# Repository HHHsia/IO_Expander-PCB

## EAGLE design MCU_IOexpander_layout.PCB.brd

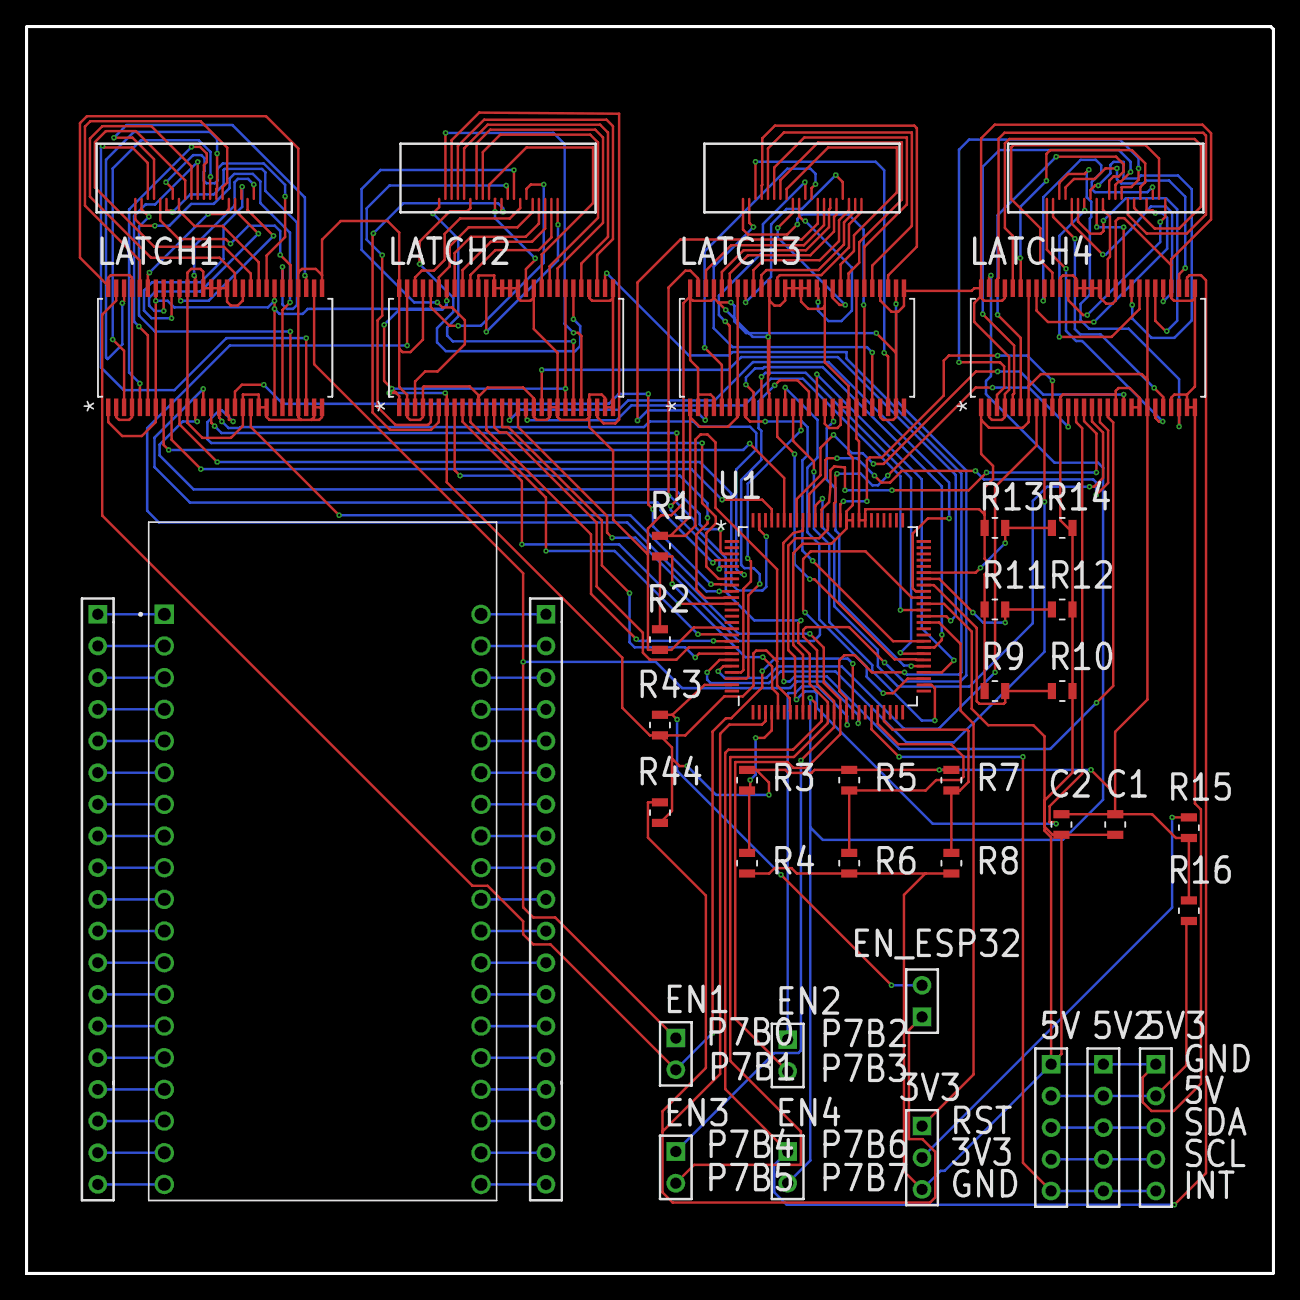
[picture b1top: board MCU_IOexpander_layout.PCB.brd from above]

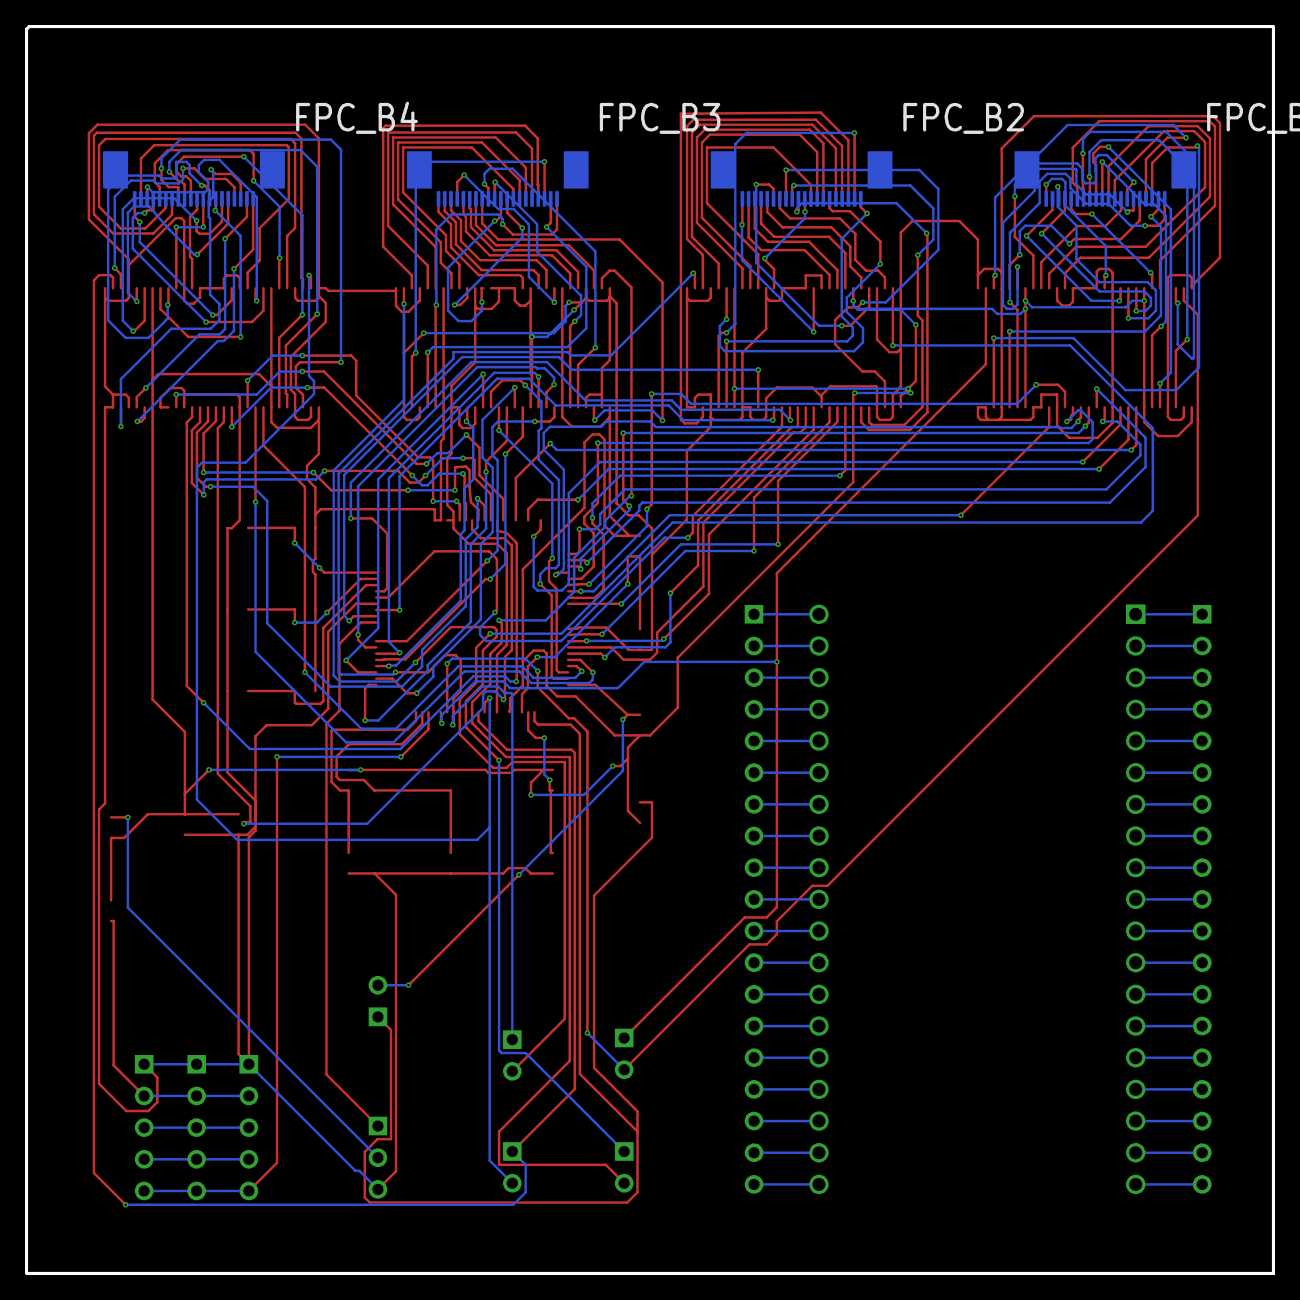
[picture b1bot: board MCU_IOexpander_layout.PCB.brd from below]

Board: 2 copper layers, 100.0 x 100.0 mm, 41 parts (4 on the bottom side), 183 nets.

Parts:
3V3: Header_3; HDR1X3_1PRIMARY
5V, 5V2: Header_5; HDR1X5_1PRIMARY
5V3: Header_5; HDR1X5_2PRIMARY
C1, C2: C0805; RES_RC0805_YAG-L_1PRIMARY
EN1: Header_2; HDR1X2_5PRIMARY
EN2: Header_2; HDR1X2_4PRIMARY
EN3: Header_2; HDR1X2_3PRIMARY
EN4: Header_2; HDR1X2_2PRIMARY
EN_ESP32: Header_2; HDR1X2_1PRIMARY
EN_ESP?, EN_ESP?2: Header_19; HDR1X19_1PRIMARY
FPC_B1: FPC__20PIN_; FPC_20PIN__B_4PRIMARY
FPC_B2: *; FPC_20PIN__B_3PRIMARY
FPC_B3: *; FPC_20PIN__B_2PRIMARY
FPC_B4: *; FPC_20PIN__B_1PRIMARY
LATCH1: SN74ALVCH162260DLR; DL56-L_4PRIMARY
LATCH2: SN74ALVCH162260DLR; DL56-L_3PRIMARY
LATCH3: SN74ALVCH162260DLR; DL56-L_2PRIMARY
LATCH4: SN74ALVCH162260DLR; DL56-L_1PRIMARY
R1, R2, R3, R4, R5, R6, R7, R8, R15, R16, R43: RC0805FR-1310KL; RES_RC0805_YAG-L_2PRIMARY
R9, R10, R11, R12, R13, R14: RC0805FR-1310KL; RES_RC0805_YAG-L_3PRIMARY
R44: RC0805FR-1310KL; RES_RC0805_YAG-L_1PRIMARY
U1: CY8C9560A-24AXI; TQFP-100-L_1PRIMARY
U?: ESP32-DEVKITC-32D; MODULE_ESP32-DEVKITC-32D_1PRIMARY

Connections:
3V3: 3V3.2, R15.2
5V: 5V.2, 5V2.2, 5V3.2, R16.1
A0: R1.1, R2.2, U1.30
FPC_1: FPC_B1.3, LATCH1.23
FPC_2: FPC_B1.4, LATCH1.24
FPC_3: FPC_B1.5, LATCH1.26
FPC_4: FPC_B1.6, LATCH1.31
FPC_5: FPC_B1.7, LATCH1.33
FPC_6: FPC_B1.8, LATCH1.34
FPC_7: FPC_B1.9, LATCH1.36
FPC_8: FPC_B1.10, LATCH1.37
FPC_9: FPC_B1.11, LATCH1.38
FPC_10: FPC_B1.12, LATCH1.40
FPC_11: FPC_B1.13, LATCH1.6
FPC_12: FPC_B1.14, LATCH1.5
FPC_13: FPC_B1.15, LATCH1.3
FPC_14: FPC_B1.16, LATCH1.54
FPC_15: FPC_B1.17, LATCH1.52
FPC_16: FPC_B1.18, LATCH1.51
FPC_17: FPC_B1.19, LATCH1.49
FPC_18: FPC_B1.20, LATCH1.48
FPC_19: FPC_B1.21, LATCH1.47
FPC_20: FPC_B1.22, LATCH1.45
FPC_21: FPC_B2.3, LATCH2.23
FPC_22: FPC_B2.4, LATCH2.24
FPC_23: FPC_B2.5, LATCH2.26
FPC_24: FPC_B2.6, LATCH2.31
FPC_25: FPC_B2.7, LATCH2.33
FPC_26: FPC_B2.8, LATCH2.34
FPC_27: FPC_B2.9, LATCH2.36
FPC_28: FPC_B2.10, LATCH2.37
FPC_29: FPC_B2.11, LATCH2.38
FPC_30: FPC_B2.12, LATCH2.40
FPC_31: FPC_B2.13, LATCH2.6
FPC_32: FPC_B2.14, LATCH2.5
FPC_33: FPC_B2.15, LATCH2.3
FPC_34: FPC_B2.16, LATCH2.54
FPC_35: FPC_B2.17, LATCH2.52
FPC_36: FPC_B2.18, LATCH2.51
FPC_37: FPC_B2.19, LATCH2.49
FPC_38: FPC_B2.20, LATCH2.48
FPC_39: FPC_B2.21, LATCH2.47
FPC_40: FPC_B2.22, LATCH2.45
FPC_41: FPC_B3.3, LATCH3.23
FPC_42: FPC_B3.4, LATCH3.24
FPC_43: FPC_B3.5, LATCH3.26
FPC_44: FPC_B3.6, LATCH3.31
FPC_45: FPC_B3.7, LATCH3.33
FPC_46: FPC_B3.8, LATCH3.34
FPC_47: FPC_B3.9, LATCH3.36
FPC_48: FPC_B3.10, LATCH3.37
FPC_49: FPC_B3.11, LATCH3.38
FPC_50: FPC_B3.12, LATCH3.40
FPC_51: FPC_B3.13, LATCH3.6
FPC_52: FPC_B3.14, LATCH3.5
FPC_53: FPC_B3.15, LATCH3.3
FPC_54: FPC_B3.16, LATCH3.54
FPC_55: FPC_B3.17, LATCH3.52
FPC_56: FPC_B3.18, LATCH3.51
FPC_57: FPC_B3.19, LATCH3.49
FPC_58: FPC_B3.20, LATCH3.48
FPC_59: FPC_B3.21, LATCH3.47
FPC_60: FPC_B3.22, LATCH3.45
FPC_61: FPC_B4.3, LATCH4.23
FPC_62: FPC_B4.4, LATCH4.24
FPC_63: FPC_B4.5, LATCH4.26
FPC_64: FPC_B4.6, LATCH4.31
FPC_65: FPC_B4.7, LATCH4.33
FPC_66: FPC_B4.8, LATCH4.34
FPC_67: FPC_B4.9, LATCH4.36
FPC_68: FPC_B4.10, LATCH4.37
FPC_69: FPC_B4.11, LATCH4.38
FPC_70: FPC_B4.12, LATCH4.40
FPC_71: FPC_B4.13, LATCH4.6
FPC_72: FPC_B4.14, LATCH4.5
FPC_73: FPC_B4.15, LATCH4.3
FPC_74: FPC_B4.16, LATCH4.54
FPC_75: FPC_B4.17, LATCH4.52
FPC_76: FPC_B4.18, LATCH4.51
FPC_77: FPC_B4.19, LATCH4.49
FPC_78: FPC_B4.20, LATCH4.48
FPC_79: FPC_B4.21, LATCH4.47
FPC_80: FPC_B4.22, LATCH4.45
GND: 3V3.3, 5V.1, 5V2.1, 5V3.1, C1.1, C2.1, LATCH1.2, LATCH1.4, LATCH1.11, LATCH1.18, LATCH1.20, LATCH1.21, LATCH1.25, LATCH1.27, LATCH1.28, LATCH1.29, LATCH1.32, LATCH1.39, LATCH1.41, LATCH1.42, LATCH1.43, LATCH1.44, LATCH1.46, LATCH1.53, LATCH1.56, LATCH2.2, LATCH2.4, LATCH2.11, LATCH2.18, LATCH2.20, LATCH2.21, LATCH2.25, LATCH2.27, LATCH2.28, LATCH2.29, LATCH2.32, LATCH2.39, LATCH2.41, LATCH2.42, LATCH2.43, LATCH2.44, LATCH2.46, LATCH2.53, LATCH2.56, LATCH3.2, LATCH3.4, LATCH3.11, LATCH3.18, LATCH3.20, LATCH3.21, LATCH3.25, LATCH3.27, LATCH3.29, LATCH3.32, LATCH3.39, LATCH3.41, LATCH3.42, LATCH3.43, LATCH3.44, LATCH3.46, LATCH3.53, LATCH3.56, LATCH4.2, LATCH4.4, LATCH4.11, LATCH4.18, LATCH4.20, LATCH4.21, LATCH4.25, LATCH4.27, LATCH4.28, LATCH4.29, LATCH4.32, LATCH4.39, LATCH4.41, LATCH4.42, LATCH4.43, LATCH4.44, LATCH4.46, LATCH4.53, LATCH4.56, R2.1, R4.1, R6.1, R8.1, R10.1, R12.1, R14.1, U1.15, U1.34, U1.65, U1.84, U1.85
INT: 5V.5, 5V2.5, 5V3.5, U1.45
J2-1: EN_ESP?2.1, U?.1
J2-2: EN_ESP?2.2, U?.2
J2-3: EN_ESP?2.3, U?.3
J2-4: EN_ESP?2.4, U?.4
J2-5: EN_ESP?2.5, U?.5
J2-6: EN_ESP?2.6, U?.6
J2-7: EN_ESP?2.7, U?.7
J2-8: EN_ESP?2.8, U?.8
J2-9: EN_ESP?2.9, U?.9
J2-10: EN_ESP?2.10, U?.10
J2-11: EN_ESP?2.11, U?.11
J2-12: EN_ESP?2.12, U?.12
J2-13: EN_ESP?2.13, U?.13
J2-14: EN_ESP?2.14, U?.14
J2-15: EN_ESP?2.15, U?.15
J2-16: EN_ESP?2.16, U?.16
J2-17: EN_ESP?2.17, U?.17
J2-18: EN_ESP?2.18, U?.18
J2-19: EN_ESP?2.19, U?.19
J3-1: EN_ESP?.1, U?.20
J3-2: EN_ESP?.2, U?.21
J3-3: EN_ESP?.3, U?.22
J3-4: EN_ESP?.4, U?.23
J3-5: EN_ESP?.5, U?.24
J3-6: EN_ESP?.6, U?.25
J3-7: EN_ESP?.7, U?.26
J3-8: EN_ESP?.8, U?.27
J3-9: EN_ESP?.9, U?.28
J3-10: EN_ESP?.10, U?.29
J3-11: EN_ESP?.11, U?.30
J3-12: EN_ESP?.12, U?.31
J3-13: EN_ESP?.13, U?.32
J3-14: EN_ESP?.14, U?.33
J3-15: EN_ESP?.15, U?.34
J3-16: EN_ESP?.16, U?.35
J3-17: EN_ESP?.17, U?.36
J3-18: EN_ESP?.18, U?.37
J3-19: EN_ESP?.19, U?.38
NETEN_ESP32_1: EN_ESP32.1, R44.2, U1.28
NETEN_ESP32_2: EN_ESP32.2, R43.2, U1.24
P0B0: LATCH1.8, U1.95
P0B1: LATCH1.9, U1.97
P0B2: LATCH1.10, U1.99
P0B3: LATCH1.12, U1.3
P0B4: LATCH1.13, U1.4
P0B5: LATCH1.14, U1.5
P0B6: LATCH1.15, U1.6
P0B7: LATCH1.16, U1.7
P1B5: R13.1, R14.2, U1.70
P1B6: R11.1, R12.2, U1.69
P1B7: R9.1, R10.2, U1.68
P2B0: R7.1, R8.2, U1.47
P2B1: R5.1, R6.2, U1.46
P2B3: R3.1, R4.2, U1.29
P3B0: LATCH1.17, U1.8
P3B1: LATCH1.19, U1.9
P3B2: LATCH2.8, U1.10
P3B3: LATCH2.9, U1.11
P3B4: LATCH2.10, U1.16
P3B5: LATCH2.12, U1.17
P3B6: LATCH2.13, U1.18
P3B7: LATCH2.14, U1.19
P4B0: LATCH2.15, U1.67
P4B1: LATCH2.16, U1.66
P4B2: LATCH2.17, U1.64
P4B3: LATCH2.19, U1.63
P4B4: LATCH3.8, U1.59
P4B5: LATCH3.9, U1.58
P4B6: LATCH3.10, U1.57
P4B7: LATCH3.12, U1.56
P5B0: LATCH3.13, U1.53
P5B1: LATCH3.14, U1.52
P5B2: LATCH3.15, U1.22
P5B3: LATCH3.16, U1.23
P5B4: LATCH3.17, U1.54
P5B5: LATCH3.19, U1.55
P5B6: LATCH4.8, U1.21
P5B7: LATCH4.9, U1.20
P6B0: LATCH4.10, U1.86
P6B1: LATCH4.12, U1.87
P6B2: LATCH4.13, U1.88
P6B3: LATCH4.14, U1.89
P6B4: LATCH4.15, U1.90
P6B5: LATCH4.16, U1.91
P6B6: LATCH4.17, U1.92
P6B7: LATCH4.19, U1.93
P7B0: EN1.1, LATCH1.30, U1.43
P7B1: EN1.2, LATCH1.55, U1.42
P7B2: EN2.1, LATCH2.30, U1.41
P7B3: EN2.2, LATCH2.55, U1.40
P7B4: EN3.1, LATCH3.30, U1.39
P7B5: EN3.2, LATCH3.55, U1.38
P7B6: EN4.1, LATCH4.30, U1.37
P7B7: EN4.2, LATCH4.55, U1.36
RST: 3V3.1, U1.62
SCL: 5V.4, 5V2.4, 5V3.4
SDA: 5V.3, 5V2.3, 5V3.3
VDD: C1.2, C2.2, LATCH1.1, LATCH1.7, LATCH1.22, LATCH1.35, LATCH1.50, LATCH2.1, LATCH2.7, LATCH2.22, LATCH2.35, LATCH2.50, LATCH3.1, LATCH3.7, LATCH3.22, LATCH3.35, LATCH3.50, LATCH4.1, LATCH4.7, LATCH4.22, LATCH4.35, LATCH4.50, R1.2, R3.2, R5.2, R7.2, R9.2, R11.2, R13.2, R15.1, R16.2, R43.1, R44.1, U1.32, U1.82, U1.83

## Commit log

2024-07-05 0705
